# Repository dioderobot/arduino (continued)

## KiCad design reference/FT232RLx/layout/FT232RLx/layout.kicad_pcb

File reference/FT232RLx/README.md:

# FT232RLx USB to Serial Converter

FTDI USB to UART bridge IC with two package options for high-quality serial communication and Arduino programming.

## Usage

```starlark
FT232RLx = Module("//reference/FT232RLx/FT232RLx.zen")

FT232RLx(
    name = "usb_serial",
    package = "FT231XQ",              # "FT231XQ" (4×4mm) or "FT232RL" (10×5mm)
    add_tx_rx_leds = True,            # Optional TX/RX indicator LEDs
    add_ferrite_bead = True,          # Optional EMI filtering on USB power
    VCC = Power("VCC"),               # 5V power supply (4.35-5.25V)
    VCCIO = Power("3V3"),             # I/O voltage (3.3V or 5V)
    USB_VCC = Power("USB_5V"),        # USB VBUS
    GND = Ground("GND"),
    USB = usb_connector,              # USB 2.0 D+/D- differential pair
    UART = mcu_uart,                  # UART interface to microcontroller
    DTR = reset_signal,               # DTR output for Arduino auto-reset
    RTS = rts_signal,                 # RTS output (optional)
    CTS = cts_signal,                 # CTS input (optional)
    CBUS0 = tx_led,                   # CBUS0/TXLED
    CBUS1 = rx_led,                   # CBUS1/RXLED
    # CBUS2-4 available as GPIO
)
```

## Package Options

### FT231XQ - Compact (Default)
- **Package**: QFN-20 (4mm × 4mm)
- **Best for**: Space-constrained designs, Arduino Nano
- **Features**: 4 CBUS pins, all essential Arduino features
- **Cost**: Lower than FT232RL

### FT232RL - Full Featured
- **Package**: SSOP-28 (10mm × 5mm)  
- **Best for**: Designs needing extra GPIO or legacy compatibility
- **Features**: 5 CBUS pins, more configuration options
- **Cost**: Higher than FT231XQ

## Features

- **USB 2.0**: Full speed (12Mbps) with built-in termination
- **UART**: Up to 3Mbps baud rate with hardware flow control
- **Oscillator**: Internal oscillator (no external crystal needed)
- **Regulator**: Built-in 3.3V regulator (50mA max on 3V3OUT pin)
- **VCCIO**: Configurable I/O voltage (3.3V or 5V logic levels)
- **Signals**: DTR, RTS, CTS for Arduino auto-reset and flow control
- **CBUS**: Configurable pins (TXLED, RXLED, GPIO, etc.)
- **EEPROM**: Internal EEPROM for USB descriptors
- **Drivers**: Native support in most operating systems

## Arduino Auto-Reset

Connect DTR through 100nF capacitor to ATmega328P reset pin:

```starlark
Capacitor(
    name = "C_AUTORESET",
    value = "100nF",
    package = "0402",
    P1 = usb_serial.DTR,
    P2 = mcu.RESET,
)
```

## VCCIO Configuration

The VCCIO pin sets the I/O voltage level:
- **5V I/O**: Connect VCCIO to VCC (5V)
- **3.3V I/O**: Connect VCCIO to 3.3V rail

This allows voltage translation between USB (5V) and 3.3V microcontrollers.

## CBUS Pins

CBUS pins can be configured via EEPROM (using FT_PROG utility):
- **CBUS0**: TXLED (default) - Blinks when transmitting
- **CBUS1**: RXLED (default) - Blinks when receiving
- **CBUS2-3**: GPIO, PWM, Clock output, etc.
- **CBUS4**: GPIO (FT232RL only)

## Notes

- **FT231XQ advantages**: Smaller (4×4mm), lower cost, adequate for Arduino
- **FT232RL advantages**: More CBUS pins, easier hand soldering (SSOP vs QFN)
- No external crystal required (internal oscillator)
- USB series resistors (27Ω) for signal integrity
- Optional ferrite bead on USB power for EMI filtering
- 3V3OUT provides max 50mA for external use
- Superior signal quality compared to CH340
- Requires FTDI drivers (usually pre-installed)
- EEPROM can store custom VID/PID and device name
- DTR/RTS are active-low signals

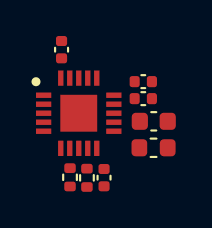
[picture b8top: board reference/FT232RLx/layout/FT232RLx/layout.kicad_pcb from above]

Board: 2 copper layers, 9 parts (0 on the bottom side), 6 nets, no tracks yet.

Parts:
C1: 100nF 6.3V; C_0402_1005Metric
C2, C3, C4: 100nF 10V; C_0402_1005Metric
C5: 4.7uF 10V; C_0603_1608Metric
IC1: FT231XQMR; QFN50P400X400X80-21N
L1: 600nH; L_0603_1608Metric
R1, R2: 27 5%; R_0402_1005Metric

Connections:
GND: C1.2, C2.2, C3.2, C4.2, C5.2, IC1.3, IC1.13, IC1.21
P3V3OUT: C1.1, IC1.10
USBDM_INTERNAL: IC1.9, R1.1
USBDP_INTERNAL: IC1.8, R2.1
VCC: C3.1, C4.1, C5.1, IC1.11, IC1.12, L1.2
VCCIO: C2.1, IC1.20

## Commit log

2025-10-21 rename board
2025-10-21 better rules
2025-10-21 add components
2025-10-21 add reference
2025-10-21 first pass
2025-10-21 blue solder mask
2025-10-21 add arduino access
2025-10-21 vendor
2025-10-21 better connector
2025-10-21 add uart LEDs
2025-10-21 Fix allowlist
2025-10-21 full routing
2025-10-22 better schematics
2025-10-22 add pcb version
2025-10-22 add UnoQ
2025-10-22 Fix CI release error and correct unoQ board configuration
    - Add quotes around board name and archive path in CI workflow to handle spaces in 'Arduino UNO Q'
    - Update unoQ Board() configuration: name, layout_path, and layers (2->4)
    - Fixes 'unexpected argument Q found' error in pcb release command
2025-10-22 Vendor stdlib HEAD dependencies for offline CI builds
    - Update stdlib from v0.3.2 to HEAD
    - Add new generics: Diode, MountingHole, TestPoint, Version
    - Add additional KiCad footprints and symbols
    - Fixes offline build errors in CI
2025-10-22 Fix CI: Add python3-pip and sanitize board names in filenames
    - Add python3-pip to dependencies for sigstore action
    - Replace spaces with underscores in archive filenames (Arduino_UNO_Q-<hash>.zip)
    - Update artifact names to use sanitized board slug
    - Fixes 'input Arduino doesn't expand to one or more filenames' error
2025-10-22 use carrier and core arch
2025-11-26 fix CI
2025-12-04 Update GitHub workflow: pcb-release.yml (#8)
2025-12-07 Bump stdlib
2025-12-07 Fix warnings
2025-12-07 Refactor into modules
    modules/NanoCarrier/
    modules/NanoCore/
    modules/Stackup/
2025-12-07 pcb migrate
2025-12-07 Update GitHub workflow: pcb-release.yml (#10)
2025-12-10 bump pcb
2025-12-12 Update GitHub workflow: pcb-release.yml (#11)
2025-12-17 Update GitHub workflow: pcb-release.yml (#12)
2026-01-09 Update GitHub workflows
2026-01-09 Update GitHub workflows (#13)
2026-01-10 Update GitHub workflows (#14)
2026-01-12 Update GitHub workflows (#15)
2026-01-15 Update GitHub workflows (#16)
2026-01-21 Update GitHub workflows (#17)
2026-01-23 Update GitHub workflows (#18)
2026-01-26 Update GitHub workflows (#19)
2026-02-02 Bump stdlib, disambiguate 2.2kOhms
2026-02-06 Update GitHub workflows (#20)
2026-02-12 Update GitHub workflows (#21)
2026-02-13 Update GitHub workflows (#22)
2026-02-16 Update GitHub workflows (#23)
2026-02-18 Update GitHub workflows (#24)
2026-02-21 Update GitHub workflows (#25)
2026-03-02 Update GitHub workflows (#26)
2026-03-02 Update GitHub workflows (#27)
2026-03-05 Update GitHub workflows (#28)
2026-03-07 Update GitHub workflows (#29)
2026-03-11 Update GitHub workflows (#30)
2026-03-28 Bump pcb version
2026-04-19 chore: flatten eda/ subdirs into their parent component packages
    Move .kicad_mod, .kicad_sym, and other files out of per-package eda/
    subdirectories up into the component package roots. Strip the eda/
    path segment from all in-repo references:
    - 30 component .zen files (Symbol library, File footprint paths)
    - 2 fp-lib-table files (boards/unoQ KIPRJMOD URIs)
    30 component packages flattened under components/. pcb build passes
2026-04-19 Update GitHub workflow: pcb-release.yml (#31)
    * Update GitHub workflows
    * chore: flatten eda/ subdirs into their parent component packages
    Move .kicad_mod, .kicad_sym, and other files out of per-package eda/
    subdirectories up into the component package roots. Strip the eda/
    path segment from all in-repo references:
    - 30 component .zen files (Symbol library, File footprint paths)
2026-04-20 Update GitHub workflows (#32)
